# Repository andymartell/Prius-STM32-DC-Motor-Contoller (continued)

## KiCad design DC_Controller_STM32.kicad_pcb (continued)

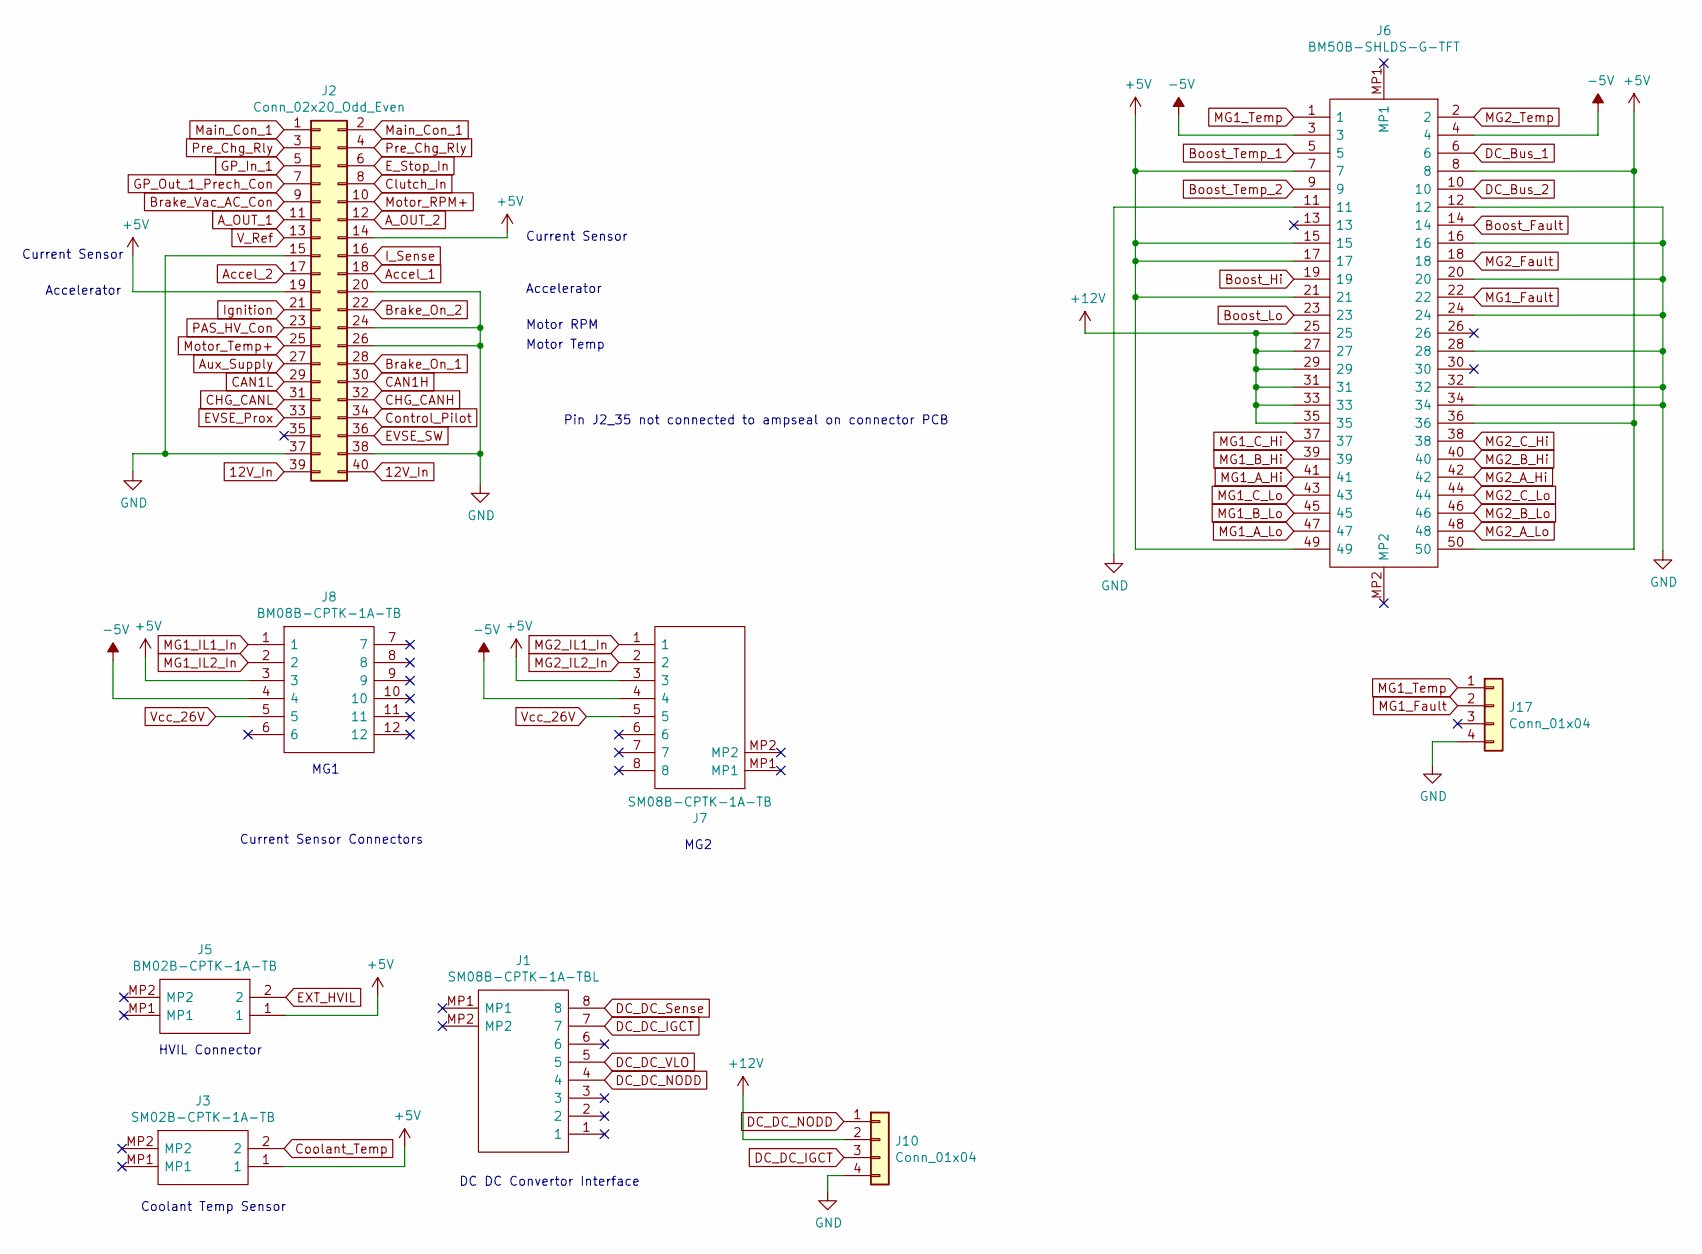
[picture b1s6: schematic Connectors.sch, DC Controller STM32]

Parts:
J1: SM08B-CPTK-1A-TBL; SM08BCPTK1ATBL; Mouser Part Number 306-SM08B-CPTK-1ATBL
J2: Conn_02x20_Odd_Even; IDC-Header_2x20_P2.54mm_Horizontal
J3: SM02B-CPTK-1A-TB; SM02BCPTK1ATB; Mouser Part Number 306-SM02B-CPTK-1A-TB
J5: BM02B-CPTK-1A-TB; BM02BCPTK1ATB; Mouser Part Number 306-BM02B-CPTK-1A-TB
J6: BM50B-SHLDS-G-TFT; BM50BSHLDSGTFT; Manufacturer_Part_Number BM50B-SHLDS-G-TFT
J7: SM08B-CPTK-1A-TB; SM08BCPTK1ATBL_odd_even; Manufacturer_Part_Number SM08B-CPTK-1A-TB
J8: BM08B-CPTK-1A-TB; BM08BCPTK1ATB; Mouser Part Number 306-BM08B-CPTK-1A-TB
J10, J17: Conn_01x04; PinHeader_1x04_P2.54mm_Vertical

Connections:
12V_In: J2.39, J2.40; also elsewhere on the board
+5V: J2.14, J2.19, J3.1, J5.1, J6.7, J6.8, J6.15, J6.17, J6.21, J6.36, J6.49, J6.50, J7.3, J8.3; also elsewhere on the board
+12V: J6.25, J6.27, J6.29, J6.31, J6.33, J6.35, J10.2; also elsewhere on the board
-5V: J6.3, J6.4, J7.4, J8.4; also elsewhere on the board
A_OUT_1: J2.11; also elsewhere on the board
A_OUT_2: J2.12; also elsewhere on the board
Accel_1: J2.18; also elsewhere on the board
Accel_2: J2.17; also elsewhere on the board
Aux_Supply: J2.27; also elsewhere on the board
Boost_Fault: J6.14; also elsewhere on the board
Boost_Hi: J6.19; also elsewhere on the board
Boost_Lo: J6.23; also elsewhere on the board
Boost_Temp_1: J6.5; also elsewhere on the board
Boost_Temp_2: J6.9; also elsewhere on the board
Brake_On_1: J2.28; also elsewhere on the board
Brake_On_2: J2.22; also elsewhere on the board
Brake_Vac_AC_Con: J2.9; also elsewhere on the board
CAN1H: J2.30; also elsewhere on the board
CAN1L: J2.29; also elsewhere on the board
CHG_CANH: J2.32; also elsewhere on the board
CHG_CANL: J2.31; also elsewhere on the board
Clutch_In: J2.8; also elsewhere on the board
Control_Pilot: J2.34; also elsewhere on the board
Coolant_Temp: J3.2; also elsewhere on the board
DC_Bus_1: J6.6; also elsewhere on the board
DC_Bus_2: J6.10; also elsewhere on the board
DC_DC_IGCT: J1.7, J10.3
DC_DC_NODD: J1.4, J10.1
DC_DC_Sense: J1.8; also elsewhere on the board
DC_DC_VLO: J1.5; also elsewhere on the board
EVSE_Prox: J2.33; also elsewhere on the board
EVSE_SW: J2.36; also elsewhere on the board
EXT_HVIL: J5.2
E_Stop_In: J2.6; also elsewhere on the board
GND: J2.15, J2.20, J2.24, J2.26, J2.37, J2.38, J6.11, J6.12, J6.16, J6.20, J6.24, J6.28, J6.32, J6.34, J10.4, J17.4; also elsewhere on the board
GP_In_1: J2.5; also elsewhere on the board
GP_Out_1_Prech_Con: J2.7; also elsewhere on the board
I_Sense: J2.16; also elsewhere on the board
Ignition: J2.21; also elsewhere on the board
MG1_A_Hi: J6.41; also elsewhere on the board
MG1_A_Lo: J6.47; also elsewhere on the board
MG1_B_Hi: J6.39; also elsewhere on the board
MG1_B_Lo: J6.45; also elsewhere on the board
MG1_C_Hi: J6.37; also elsewhere on the board
MG1_C_Lo: J6.43; also elsewhere on the board
MG1_Fault: J6.22, J17.2
MG1_IL1_In: J8.1; also elsewhere on the board
MG1_IL2_In: J8.2; also elsewhere on the board
MG1_Temp: J6.1, J17.1
MG2_A_Hi: J6.42; also elsewhere on the board
MG2_A_Lo: J6.48; also elsewhere on the board
MG2_B_Hi: J6.40; also elsewhere on the board
MG2_B_Lo: J6.46; also elsewhere on the board
MG2_C_Hi: J6.38; also elsewhere on the board
MG2_C_Lo: J6.44; also elsewhere on the board
MG2_Fault: J6.18; also elsewhere on the board
MG2_IL1_In: J7.1; also elsewhere on the board
MG2_IL2_In: J7.2; also elsewhere on the board
MG2_Temp: J6.2; also elsewhere on the board
Main_Con_1: J2.1, J2.2; also elsewhere on the board
Motor_RPM+: J2.10; also elsewhere on the board
Motor_Temp+: J2.25; also elsewhere on the board
PAS_HV_Con: J2.23; also elsewhere on the board
Pre_Chg_Rly: J2.3, J2.4; also elsewhere on the board
V_Ref: J2.13; also elsewhere on the board
Vcc_26V: J7.5, J8.5; also elsewhere on the board

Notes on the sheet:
Current Sensor
Accelerator
Motor RPM
Motor Temp
DC DC Convertor Interface
HVIL Connector
Coolant Temp Sensor
Current Sensor Connectors
MG1
MG2
Pin J2_35 not connected to ampseal on connector PCB

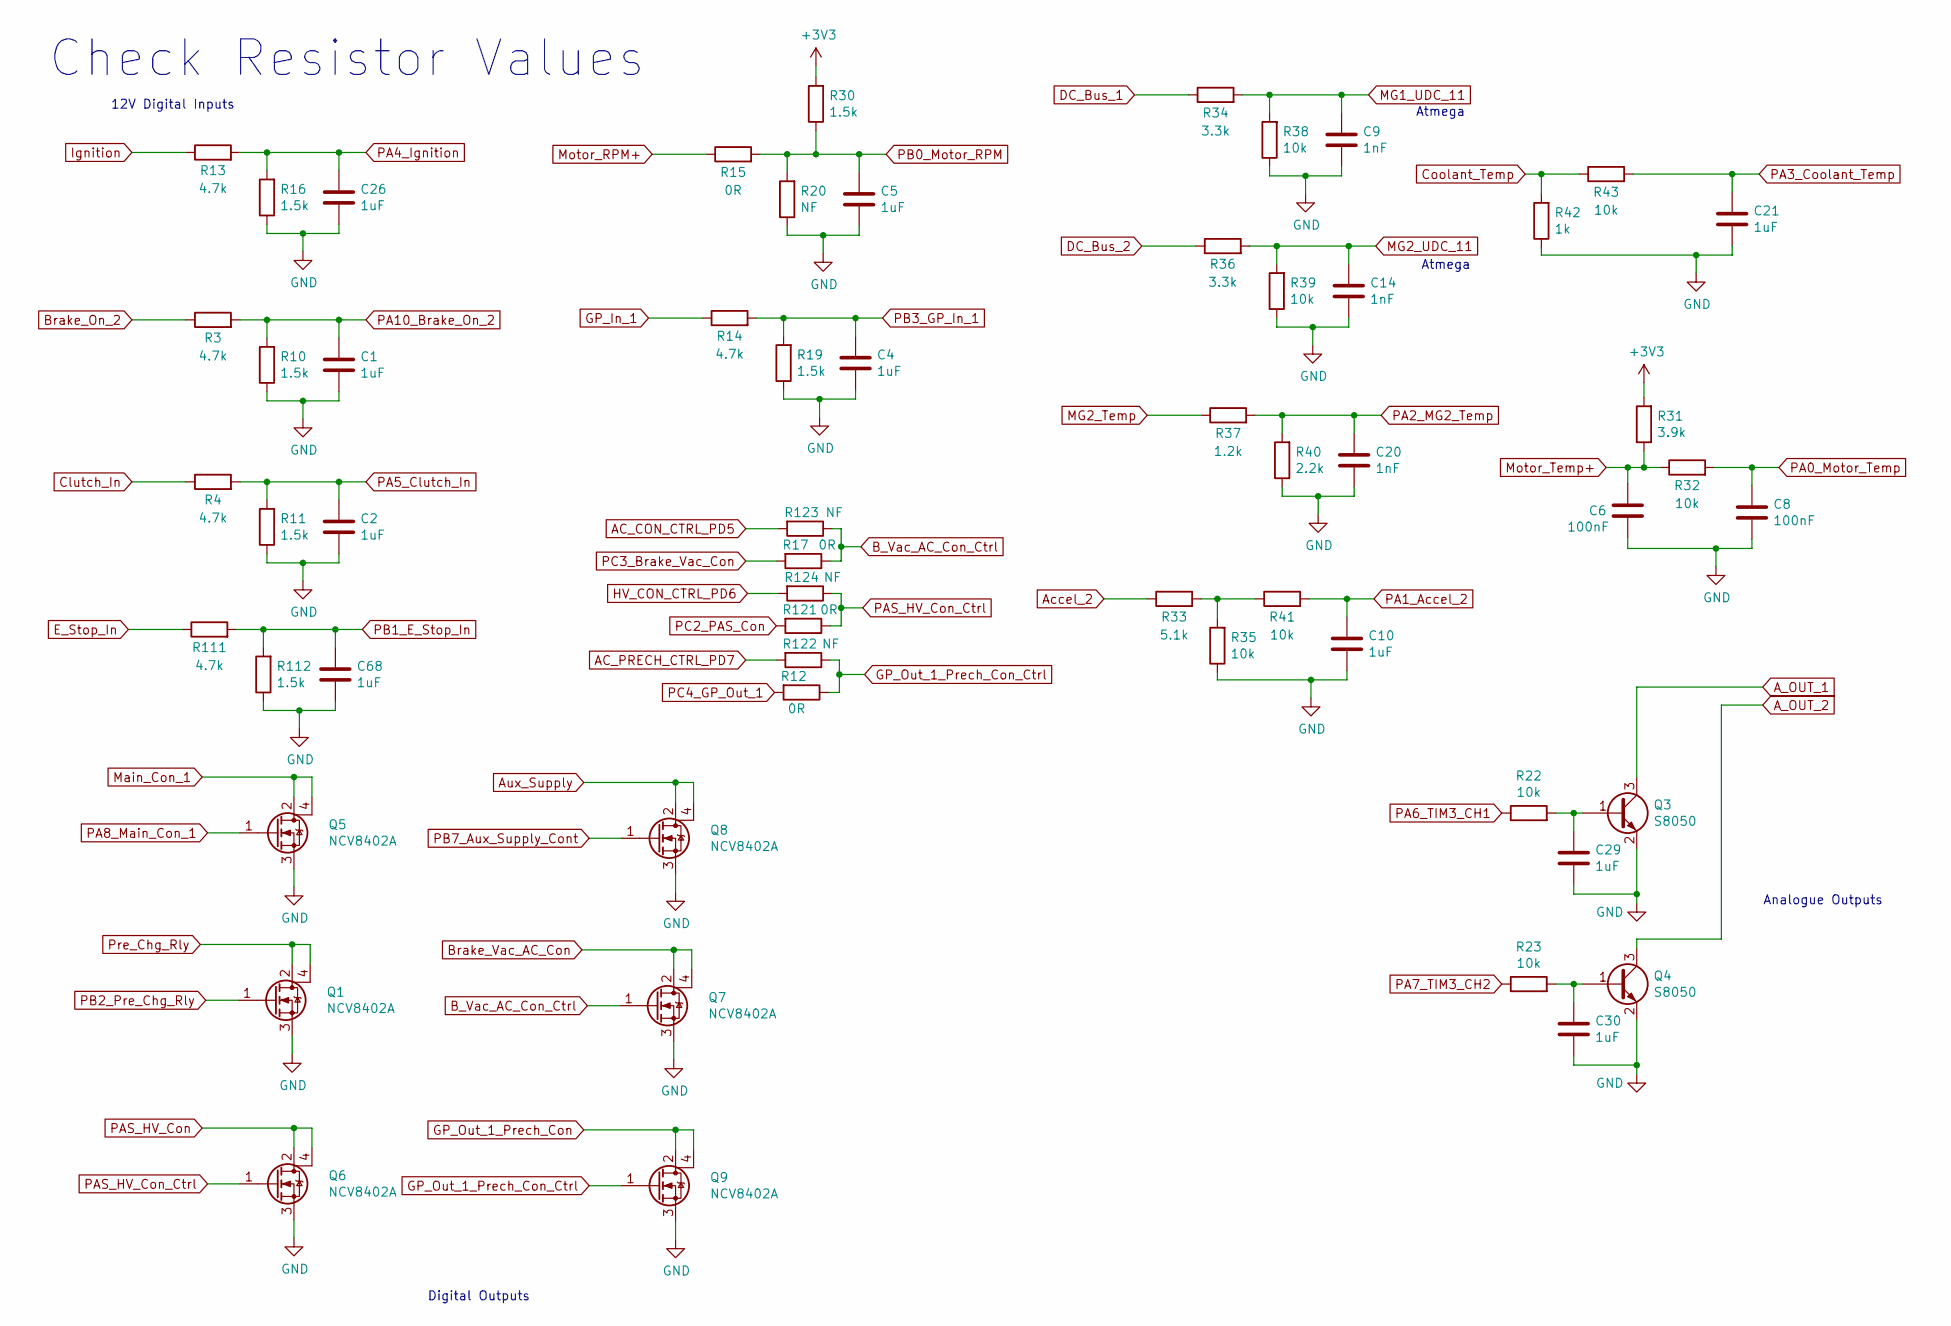
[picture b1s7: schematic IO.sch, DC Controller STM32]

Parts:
C1, C2, C4, C5, C10, C21, C26, C29, C30, C68: 1uF; C_0603_1608Metric
C6, C8: 100nF; C_0603_1608Metric
C9, C14, C20: 1nF; C_0603_1608Metric
Q1, Q5, Q6, Q7, Q8, Q9: NCV8402A; SOT-223
Q3, Q4: S8050; SOT-23
R3, R4, R13, R14, R111: 4.7k; R_0603_1608Metric
R10, R11, R16, R19, R30, R112: 1.5k; R_0603_1608Metric
R12, R15, R17, R121: 0R; R_0603_1608Metric
R20, R122, R123, R124: NF; R_0603_1608Metric
R22, R23, R32, R35, R38, R39, R41, R43: 10k; R_0603_1608Metric
R31: 3.9k; R_0603_1608Metric
R33: 5.1k; R_0603_1608Metric
R34, R36: 3.3k; R_0603_1608Metric
R37: 1.2k; R_0603_1608Metric
R40: 2.2k; R_0603_1608Metric
R42: 1k; R_0603_1608Metric

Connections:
+3V3: R30.2, R31.2; also elsewhere on the board
AC_CON_CTRL_PD5: R123.2; also elsewhere on the board
AC_PRECH_CTRL_PD7: R122.2; also elsewhere on the board
A_OUT_1: Q3.3 (C); also elsewhere on the board
A_OUT_2: Q4.3 (C); also elsewhere on the board
Accel_2: R33.1; also elsewhere on the board
Aux_Supply: Q8.2 (D), Q8.4 (D); also elsewhere on the board
B_Vac_AC_Con_Ctrl: Q7.1 (G), R17.1, R123.1
Brake_On_2: R3.1; also elsewhere on the board
Brake_Vac_AC_Con: Q7.2 (D), Q7.4 (D); also elsewhere on the board
Clutch_In: R4.1; also elsewhere on the board
Coolant_Temp: R42.2, R43.1; also elsewhere on the board
DC_Bus_1: R34.1; also elsewhere on the board
DC_Bus_2: R36.1; also elsewhere on the board
E_Stop_In: R111.1; also elsewhere on the board
GND: C1.2, C2.2, C4.2, C5.2, C6.2, C8.2, C9.2, C10.2, C14.2, C20.2, C21.2, C26.2, C29.2, C30.2, C68.2, Q1.3 (S), Q3.2 (E), Q4.2 (E), Q5.3 (S), Q6.3 (S), Q7.3 (S), Q8.3 (S), Q9.3 (S), R10.1, R11.1, R16.1, R19.1, R20.1, R35.1, R38.1, R39.1, R40.1, R42.1, R112.1; also elsewhere on the board
GP_In_1: R14.1; also elsewhere on the board
GP_Out_1_Prech_Con: Q9.2 (D), Q9.4 (D); also elsewhere on the board
GP_Out_1_Prech_Con_Ctrl: Q9.1 (G), R12.1, R122.1
HV_CON_CTRL_PD6: R124.2; also elsewhere on the board
Ignition: R13.1; also elsewhere on the board
MG1_UDC_11: C9.1, R34.2, R38.2; also elsewhere on the board
MG2_Temp: R37.1; also elsewhere on the board
MG2_UDC_11: C14.1, R36.2, R39.2; also elsewhere on the board
Main_Con_1: Q5.2 (D), Q5.4 (D); also elsewhere on the board
Motor_RPM+: R15.1; also elsewhere on the board
Motor_Temp+: C6.1, R31.1, R32.1; also elsewhere on the board
unnamed: C29.1, Q3.1 (B), R22.2
unnamed: C30.1, Q4.1 (B), R23.2
unnamed: R33.2, R35.2, R41.1
PA0_Motor_Temp: C8.1, R32.2; also elsewhere on the board
PA1_Accel_2: C10.1, R41.2; also elsewhere on the board
PA2_MG2_Temp: C20.1, R37.2, R40.2; also elsewhere on the board
PA3_Coolant_Temp: C21.1, R43.2; also elsewhere on the board
PA4_Ignition: C26.1, R13.2, R16.2; also elsewhere on the board
PA5_Clutch_In: C2.1, R4.2, R11.2; also elsewhere on the board
PA6_TIM3_CH1: R22.1; also elsewhere on the board
PA7_TIM3_CH2: R23.1; also elsewhere on the board
PA8_Main_Con_1: Q5.1 (G); also elsewhere on the board
PA10_Brake_On_2: C1.1, R3.2, R10.2; also elsewhere on the board
PAS_HV_Con: Q6.2 (D), Q6.4 (D); also elsewhere on the board
PAS_HV_Con_Ctrl: Q6.1 (G), R121.1, R124.1
PB0_Motor_RPM: C5.1, R15.2, R20.2, R30.1; also elsewhere on the board
PB1_E_Stop_In: C68.1, R111.2, R112.2; also elsewhere on the board
PB2_Pre_Chg_Rly: Q1.1 (G); also elsewhere on the board
PB3_GP_In_1: C4.1, R14.2, R19.2; also elsewhere on the board
PB7_Aux_Supply_Cont: Q8.1 (G); also elsewhere on the board
PC2_PAS_Con: R121.2; also elsewhere on the board
PC3_Brake_Vac_Con: R17.2; also elsewhere on the board
PC4_GP_Out_1: R12.2; also elsewhere on the board
Pre_Chg_Rly: Q1.2 (D), Q1.4 (D); also elsewhere on the board

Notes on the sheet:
Analogue Outputs
12V Digital Inputs
Digital Outputs
Check Resistor Values
Atmega

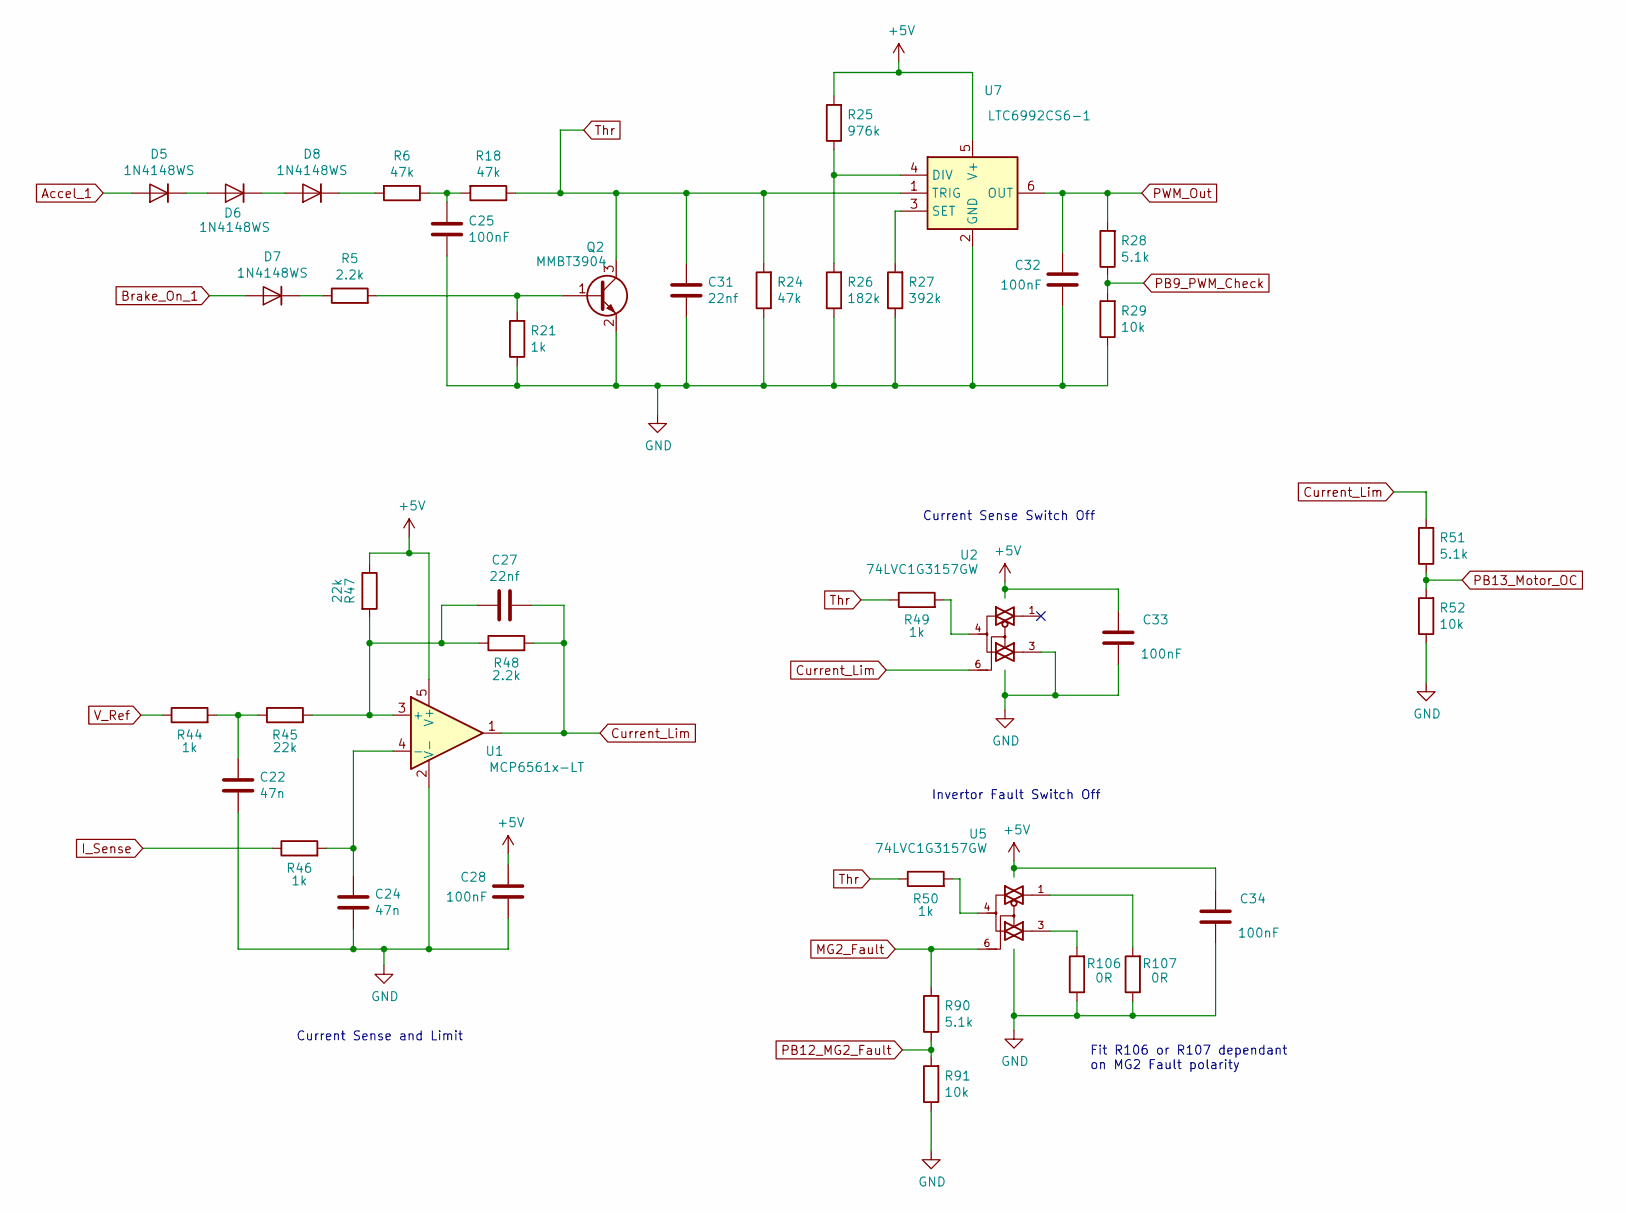
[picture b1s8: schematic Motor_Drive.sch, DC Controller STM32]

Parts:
C22, C24: 47n; C_0603_1608Metric
C25, C28, C32, C33, C34: 100nF; C_0603_1608Metric
C27, C31: 22nf; C_0603_1608Metric
D5, D6, D7, D8: 1N4148WS; D_SOD-323
Q2: MMBT3904; SOT-23
R5, R48: 2.2k; R_0603_1608Metric
R6, R18, R24: 47k; R_0603_1608Metric
R21, R44, R46, R49, R50: 1k; R_0603_1608Metric
R25: 976k; R_0805_2012Metric
R26: 182k; R_0805_2012Metric
R27: 392k; R_0805_2012Metric
R28, R51, R90: 5.1k; R_0603_1608Metric
R29, R52, R91: 10k; R_0603_1608Metric
R45, R47: 22k; R_0603_1608Metric
R106, R107: 0R; R_0603_1608Metric
U1: MCP6561x-LT; SOT-353_SC-70-5
U2, U5: 74LVC1G3157GW; SOT-363_SC-70-6
U7: LTC6992CS6-1; TSOT-23-6

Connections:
+5V: C28.1, C33.1, C34.1, R25.2, R47.1, U1.5 (V+), U2.5 (VCC), U5.5 (VCC), U7.5 (V+); also elsewhere on the board
Accel_1: D5.2 (A); also elsewhere on the board
Brake_On_1: D7.2 (A); also elsewhere on the board
Current_Lim: C27.1, R48.2, R51.2, U1.1, U2.6
GND: C22.2, C24.2, C25.2, C28.2, C31.2, C32.2, C33.2, C34.2, Q2.2 (E), R21.1, R24.1, R26.1, R27.1, R29.1, R52.1, R91.1, R106.1, R107.1, U1.2 (V-), U2.2 (GND), U2.3, U5.2 (GND), U7.2 (GND); also elsewhere on the board
I_Sense: R46.1; also elsewhere on the board
MG2_Fault: R90.2, U5.6; also elsewhere on the board
unnamed: C22.1, R44.2, R45.1
unnamed: C24.1, R46.2, U1.4 (-)
unnamed: C25.1, R6.1, R18.2
unnamed: C27.2, R45.2, R47.2, R48.1, U1.3 (+)
unnamed: D5.1 (K), D6.2 (A)
unnamed: D6.1 (K), D8.2 (A)
unnamed: D7.1 (K), R5.1
unnamed: D8.1 (K), R6.2
unnamed: Q2.1 (B), R5.2, R21.2
unnamed: R25.1, R26.2, U7.4 (DIV)
unnamed: R27.2, U7.3 (SET)
unnamed: R49.2, U2.4
unnamed: R50.2, U5.4
unnamed: R106.2, U5.3
unnamed: R107.2, U5.1
PB9_PWM_Check: R28.1, R29.2; also elsewhere on the board
PB12_MG2_Fault: R90.1, R91.2; also elsewhere on the board
PB13_Motor_OC: R51.1, R52.2; also elsewhere on the board
PWM_Out: C32.1, R28.2, U7.6 (OUT); also elsewhere on the board
Thr: C31.1, Q2.3 (C), R18.1, R24.2, R49.1, R50.1, U7.1 (TRIG)
V_Ref: R44.1; also elsewhere on the board

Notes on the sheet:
Current Sense and Limit
Current Sense Switch Off
Invertor Fault Switch Off
Fit R106 or R107 dependant on MG2 Fault polarity

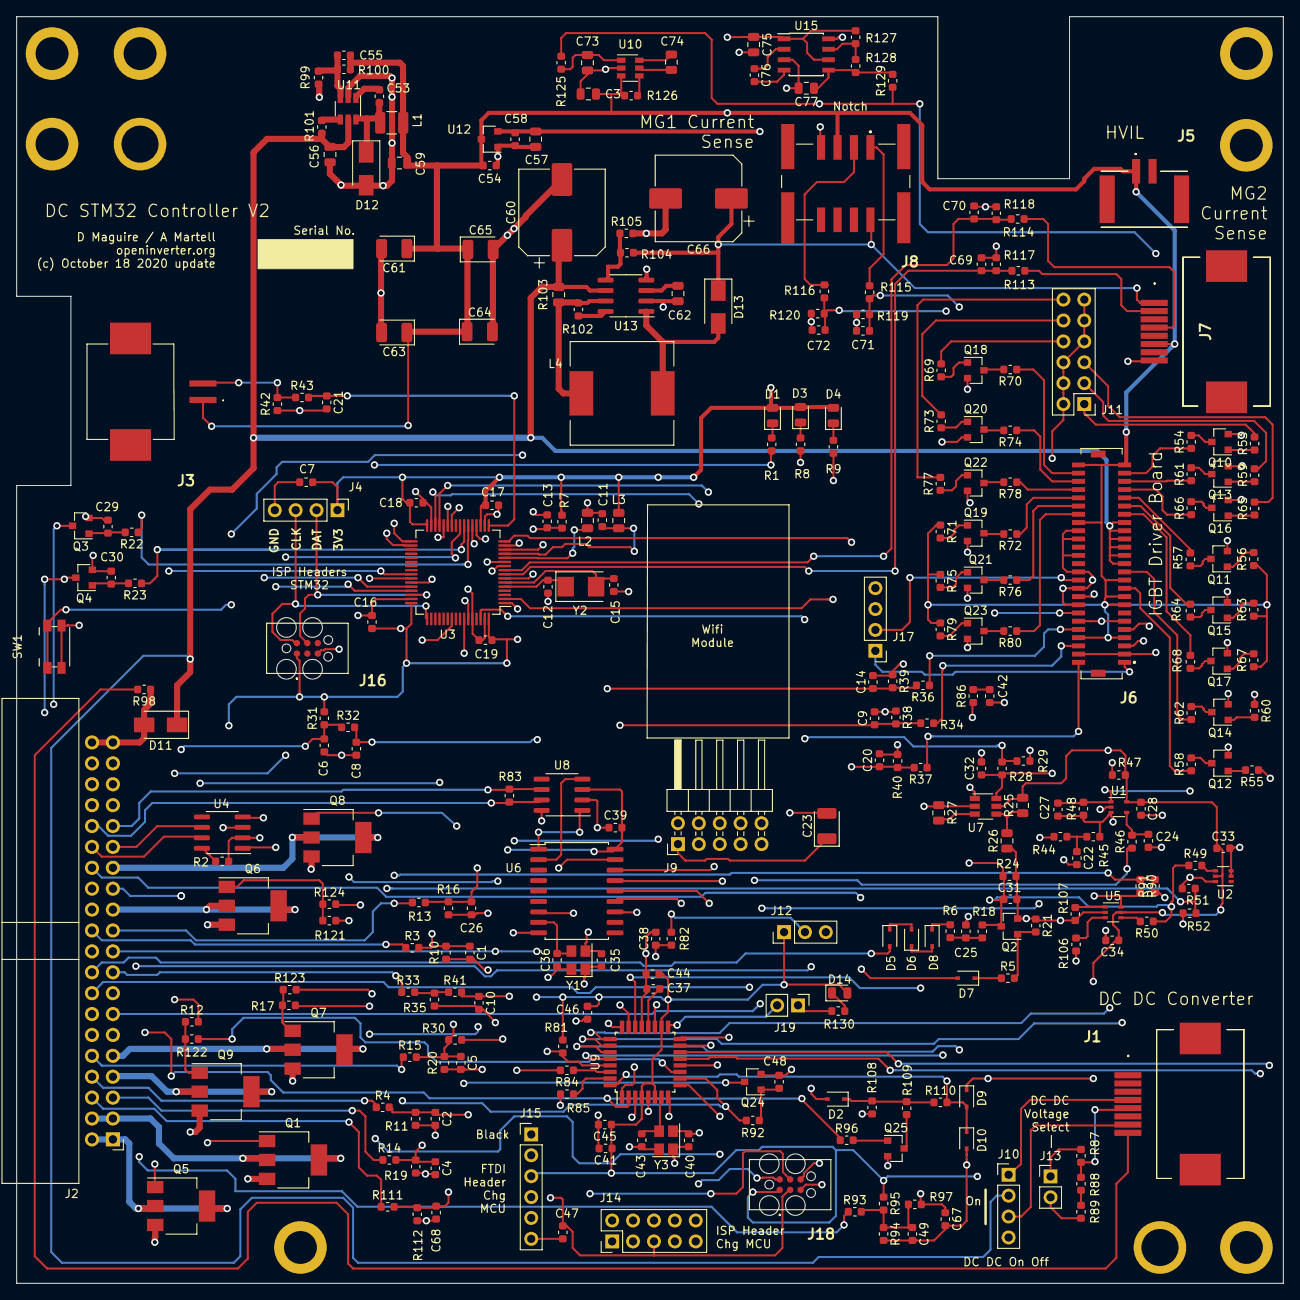
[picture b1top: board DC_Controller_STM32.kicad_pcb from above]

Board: 4 copper layers, 154.0 x 154.0 mm, 293 parts (0 on the bottom side), 223 nets.

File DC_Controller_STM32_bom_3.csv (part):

Component,Description,Part,References,Value,Footprint,Quantity Per PCB,Datasheet,JLPCB Component,JLPCB Extended,Mouser Part Number,Manufacturer_Name,Height,Mouser Price/Stock,Manufacturer_Part_Number,Arrow Part Number
1,Unpolarized capacitor,C,C6 C7 C8 C11 C13 C16 C17 C18 C19 C25 C28 C32 C33 C34 C37 C38 C39 C41 C44 C45 C46 C47 C48,100nF,C_0603_1608Metric,23,~,C14663,,,,,,,
2,Unpolarized capacitor,C,C23,100uF,CP_EIA-3528-21_Kemet-B,1,~,C16133,,,,,,,
3,Polarized capacitor,CP,C61 C63 C64 C65,100uF,CP_EIA-3528-21_Kemet-B,4,~,C16133,,,,,,,
4,Unpolarized capacitor,C,C57 C75 C77,10uF,C_0805_2012Metric,3,~,C15850,,,,,,,
5,Unpolarized capacitor,C,C62,1n5,C_0805_2012Metric,1,~,C1717,,,,,,,
6,Unpolarized capacitor,C,C9 C14 C20 C69 C70 C71 C72,1nF,C_0603_1608Metric,7,~,C1588,,,,,,,
7,Unpolarized capacitor,C,C1 C2 C4 C5 C10 C21 C26 C29 C30 C49 C54 C58 C67 C68 C76,1uF,C_0603_1608Metric,15,~,C15849,,,,,,,
8,Unpolarized capacitor,C,C74,1uF,C_0805_2012Metric,1,~,C15849,,,,,,,
9,Unpolarized capacitor,C,C12 C15 C35 C36 C40 C42 C43,20pF,C_0603_1608Metric,7,~,C1648,,,,,,,
10,Unpolarized capacitor,C,C27 C31 C53,22nf,C_0603_1608Metric,3,~,C21122,,,,,,,
11,Unpolarized capacitor,C,C59,22uF,C_0805_2012Metric,1,~,C45783,,,,,,,
12,Polarized capacitor,CP,C60 C66,330uF,CP_Elec_10x10,2,~,C134522,e,,,,,,
13,Unpolarized capacitor,C,C55,33pF,C_0603_1608Metric,1,~,C1663,,,,,,,
14,Unpolarized capacitor,C,C3 C56 C73,4.7uF,C_0805_2012Metric,3,~,C1779,,,,,,,
15,Unpolarized capacitor,C,C22 C24,47n,C_0603_1608Metric,2,~,C1622,,,,,,,
16,"75V 0.15A Fast Switching Diode, SOD-123",1N4148W,D2 D5 D6 D7 D8 D9 D10,1N4148WS,D_SOD-323,7,https://www.vishay.com/docs/85748/1n4148w.pdf,C2128,,,,,,,
17,Light emitting diode,LED,D1 D3 D4 D14,LED,LED_0805_2012Metric,4,~,C84256,,,,,,,
18,Diode,D,D11,SS54B,D_SMA,1,~,C22452,,,,,,,
19,Schottky diode,D_Schottky,D12 D13,SS54B,D_SMA,2,~,C22452,,,,,,,
20,"JST (JAPAN SOLDERLESS TERMINALS) - BM02B-CPTK-1A-TB - CONNECTOR, HEADER, 2POS, 1ROW, 2MM",BM02B-CPTK-1A-TB,J5,BM02B-CPTK-1A-TB,BM02BCPTK1ATB,1,http://www.jst-mfg.com/product/pdf/eng/eCPT.pdf,,,306-BM02B-CPTK-1A-TB,JST (JAPAN SOLDERLESS TERMINALS),11.7,https://www.mouser.co.uk/ProductDetail/JST-Automotive/BM02B-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,BM02B-CPTK-1A-TB,
21,Header Top 8 Double CPT,BM08B-CPTK-1A-TB,J8,BM08B-CPTK-1A-TB,BM08BCPTK1ATB,1,http://www.jst-mfg.com/product/pdf/eng/eCPT.pdf,,,306-BM08B-CPTK-1A-TB,JST (JAPAN SOLDERLESS TERMINALS),12,https://www.mouser.co.uk/ProductDetail/JST-Automotive/BM08B-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,BM08B-CPTK-1A-TB,
22,"Top Entry disconnectable, crimp style Shrouded Header, 50 positions",BM50B-SHLDS-G-TFT,J6,BM50B-SHLDS-G-TFT,BM50BSHLDSGTFT,1,http://www.jst-mfg.com/product/pdf/eng/eSHLD.pdf,,,,JST (JAPAN SOLDERLESS TERMINALS),4.05,,BM50B-SHLDS-G-TFT,
23,"Generic connector, single row, 01x02, script generated (kicad-library-utils/schlib/autogen/connector/)",Conn_01x02,J13 J19,Conn_01x02,PinHeader_1x02_P2.54mm_Vertical,2,~,,,,,,,,
24,"Generic connector, single row, 01x03, script generated (kicad-library-utils/schlib/autogen/connector/)",Conn_01x03,J12,Conn_01x03,PinHeader_1x03_P2.54mm_Vertical,1,~,,,,,,,,
25,"Generic connector, single row, 01x04, script generated (kicad-library-utils/schlib/autogen/connector/)",Conn_01x04,J4 J10 J17,Conn_01x04,PinHeader_1x04_P2.54mm_Vertical,3,~,,,,,,,,
26,"Generic connector, single row, 01x06, script generated (kicad-library-utils/schlib/autogen/connector/)",Conn_01x06,J15,Conn_01x06,PinHeader_1x06_P2.54mm_Vertical,1,~,,,,,,,,
27,"Generic connector, double row, 02x05, odd/even pin numbering scheme (row 1 odd numbers, row 2 even numbers), script generated (kicad-library-utils/schlib/autogen/connector/)",Conn_02x05_Odd_Even,J14,Conn_02x05_Odd_Even,PinHeader_2x05_P2.54mm_Vertical,1,~,,,,,,,,
28,"Generic connector, double row, 02x05, odd/even pin numbering scheme (row 1 odd numbers, row 2 even numbers), script generated (kicad-library-utils/schlib/autogen/connector/)",Conn_02x05_Odd_Even,J9,Conn_02x05_Odd_Even,PinHeader_2x05_P2.54mm_Horizontal,1,~,,,,,,,,
29,"Generic connector, double row, 02x06, odd/even pin numbering scheme (row 1 odd numbers, row 2 even numbers), script generated (kicad-library-utils/schlib/autogen/connector/)",Conn_02x06_Odd_Even,J11,Conn_02x06_Odd_Even,PinHeader_2x06_P2.54mm_Vertical,1,~,,,,,,,,
30,"Generic connector, double row, 02x20, odd/even pin numbering scheme (row 1 odd numbers, row 2 even numbers), script generated (kicad-library-utils/schlib/autogen/connector/)",Conn_02x20_Odd_Even,J2,Conn_02x20_Odd_Even,IDC-Header_2x20_P2.54mm_Horizontal,1,~,,,,,,,,
31,"JST (JAPAN SOLDERLESS TERMINALS) - SM02B-CPTK-1A-TB - CONNECTOR, HEADER, 2POS, 1ROW, 2MM",SM02B-CPTK-1A-TB,J3,SM02B-CPTK-1A-TB,SM02BCPTK1ATB,1,https://www.jst.co.uk/downloads/series/eCPT_(15-08-31).pdf,,,306-SM02B-CPTK-1A-TB,JST (JAPAN SOLDERLESS TERMINALS),6.8,https://www.mouser.co.uk/ProductDetail/JST-Automotive/SM02B-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,SM02B-CPTK-1A-TB,
32,Automotive Connectors SIDE ENTRY CPT HDR 2.0MM PITCH,SM08B-CPTK-1A-TBL,J7,SM08B-CPTK-1A-TB,SM08BCPTK1ATBL_odd_even,1,http://www.jst-mfg.com/product/pdf/eng/eCPT.pdf,,,,JST (JAPAN SOLDERLESS TERMINALS),12,,SM08B-CPTK-1A-TB,
33,Automotive Connectors SIDE ENTRY CPT HDR 2.0MM PITCH,SM08B-CPTK-1A-TBL,J1,SM08B-CPTK-1A-TBL,SM08BCPTK1ATBL,1,http://www.jst-mfg.com/product/pdf/eng/eCPT.pdf,,,306-SM08B-CPTK-1ATBL,JST (JAPAN SOLDERLESS TERMINALS),9.3,https://www.mouser.co.uk/ProductDetail/JST-Automotive/SM08B-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,SM08B-CPTK-1A-TBL,
34,CABLE TAG-CONNECT IN-CIRCUIT LEG,TC2030-MCP,J16 J18,TC2030-MCP,TC2030MCP,2,http://www.tag-connect.com/Materials/TC2030-MCP%20Datasheet.pdf,,,,Tag Connect,18.669,,TC2030-MCP,TC2030-MCP
35,"Inductor, small symbol",L_Small,L2 L3,10uH,L_0805_2012Metric,2,~,C1046,e,,,,,,
36,Inductor,L,L4,220uH,L_12x12mm_H6mm,1,~,C169402,e,,,,,,
37,Inductor,L,L1,4.7uH,L_1210_3225Metric,1,~,C76842,e,,,,,,
38,"0.2A Ic, 40V Vce, Small Signal NPN Transistor, SOT-23",MMBT3904,Q2 Q10 Q11 Q12 Q13 Q14 Q15 Q16 Q17 Q18 Q19 Q20 Q21 Q22 Q23 Q24 Q25,MMBT3904,SOT-23,17,https://www.fairchildsemi.com/datasheets/2N/2N3904.pdf,C20526,,,,,,,
39,"N-MOSFET transistor, gate/drain/source, drain connected to mounting plane",Q_NMOS_GDSD,Q1 Q5 Q6 Q7 Q8 Q9,NCV8402A,SOT-223,6,~,C77755,e,,,,,,
40,"NPN transistor, base/emitter/collector",Q_NPN_BEC,Q3 Q4,S8050,SOT-23,2,~,C2146,,,,,,,
41,Resistor,R,R103,0.22R,R_0805_2012Metric,1,~,C36234,e,,,,,,
42,Resistor,R,R12 R15 R17 R93 R98 R106 R107 R121 R125,0R,R_0603_1608Metric,9,~,C21189,,,,,,,
43,Resistor,R,R37,1.2k,R_0603_1608Metric,1,~,C22765,,,,,,,
44,Resistor,R,R10 R11 R16 R19 R30 R109 R112,1.5k,R_0603_1608Metric,7,~,C22843,,,,,,,
45,Resistor,R,R54 R57 R58 R61 R62 R64 R66 R68 R70 R72 R74 R76 R78 R80,100R,R_0603_1608Metric,14,~,C22775,,,,,,,
46,Resistor,R,R87 R88 R89 R101,100k,R_0603_1608Metric,4,~,C25803,,,,,,,
47,Resistor,R,R2 R7 R22 R23 R29 R32 R35 R38 R39 R41 R43 R52 R81 R91 R97,10k,R_0603_1608Metric,15,~,C25804,,,,,,,
48,Resistor,R,R83,120R,R_0603_1608Metric,1,~,C22787,,,,,,,
49,Resistor,R,R102,180R,R_0603_1608Metric,1,~,C22828,,,,,,,
50,Resistor,R,R26,182k,R_0805_2012Metric,1,~,,,,,,,,
51,Resistor,R,R21 R42 R44 R46 R49 R50 R53 R55 R56 R59 R60 R63 R65 R67 R69 R71 R73 R75 R77 R79 R82 R84 R85 R92 R96 R126,1k,R_0603_1608Metric,26,~,C21190,,,,,,,
52,Resistor,R,R5 R40 R48,2.2k,R_0603_1608Metric,3,~,C4190,,,,,,,
53,Resistor,R,R105,2.4k,R_0603_1608Metric,1,~,C22940,,,,,,,
54,Resistor,R,R108,2.7k,R_0603_1608Metric,1,~,C13167,,,,,,,
55,Resistor,R,R45 R47 R110,22k,R_0603_1608Metric,3,~,C31850,,,,,,,
56,Resistor,R,R34 R36,3.3k,R_0603_1608Metric,2,~,C22978,,,,,,,
57,Resistor,R,R117 R118 R119 R120,3.6k,R_0603_1608Metric,4,~,C22980,,,,,,,
58,Resistor,R,R31,3.9k,R_0603_1608Metric,1,~,C23018,,,,,,,
59,Resistor,R,R95,330R,R_0603_1608Metric,1,~,C23138,,,,,,,
60,Resistor,R,R27,392k,R_0805_2012Metric,1,~,,,,,,,,
61,Resistor,R,R3 R4 R13 R14 R111,4.7k,R_0603_1608Metric,5,~,C23162,,,,,,,
62,Resistor,R,R100,43k,R_0603_1608Metric,1,~,C23172,,,,,,,
63,Resistor,R,R1 R8 R9 R130,470R,R_0603_1608Metric,4,~,C23179,,,,,,,
64,Resistor,R,R6 R18 R24 R104,47k,R_0603_1608Metric,4,~,C25819,,,,,,,
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
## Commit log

2020-10-17 Initial commit for manufacture
2020-10-17 added a readme file!
2020-10-17 updated readme file. Quite boring really
2020-10-18 removed SG3204 and TX4313 -5V charge pumps and added LM2776 in their place
2020-10-18 added gitignore file
2020-10-18 updated file names to make it easier to use git!
2020-10-18 corrected tracking error around MG1 and MG current sensors. J7 footprint updated (J1 left unchanged as tracking layout is currently ok).
2020-10-18 updated readme file!
